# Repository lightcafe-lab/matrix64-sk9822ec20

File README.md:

# matrix64-sk9822ec20
 SK9822-EC20を使用した8×8のLEDマトリクスです<br><br>
LIGHTCAFE LAB LED-Cube ブログページ<br>
https://lab.lightcafe.co.jp/blog/ledcube-list<br><br>

<br>
## ライセンスについて
この 作品 は <a rel="license" href="https://creativecommons.org/licenses/by-sa/4.0/deed.ja">クリエイティブ・コモンズ 表示 - 継承 4.0 国際 ライセンス</a>の下に提供されています<br>
<br />

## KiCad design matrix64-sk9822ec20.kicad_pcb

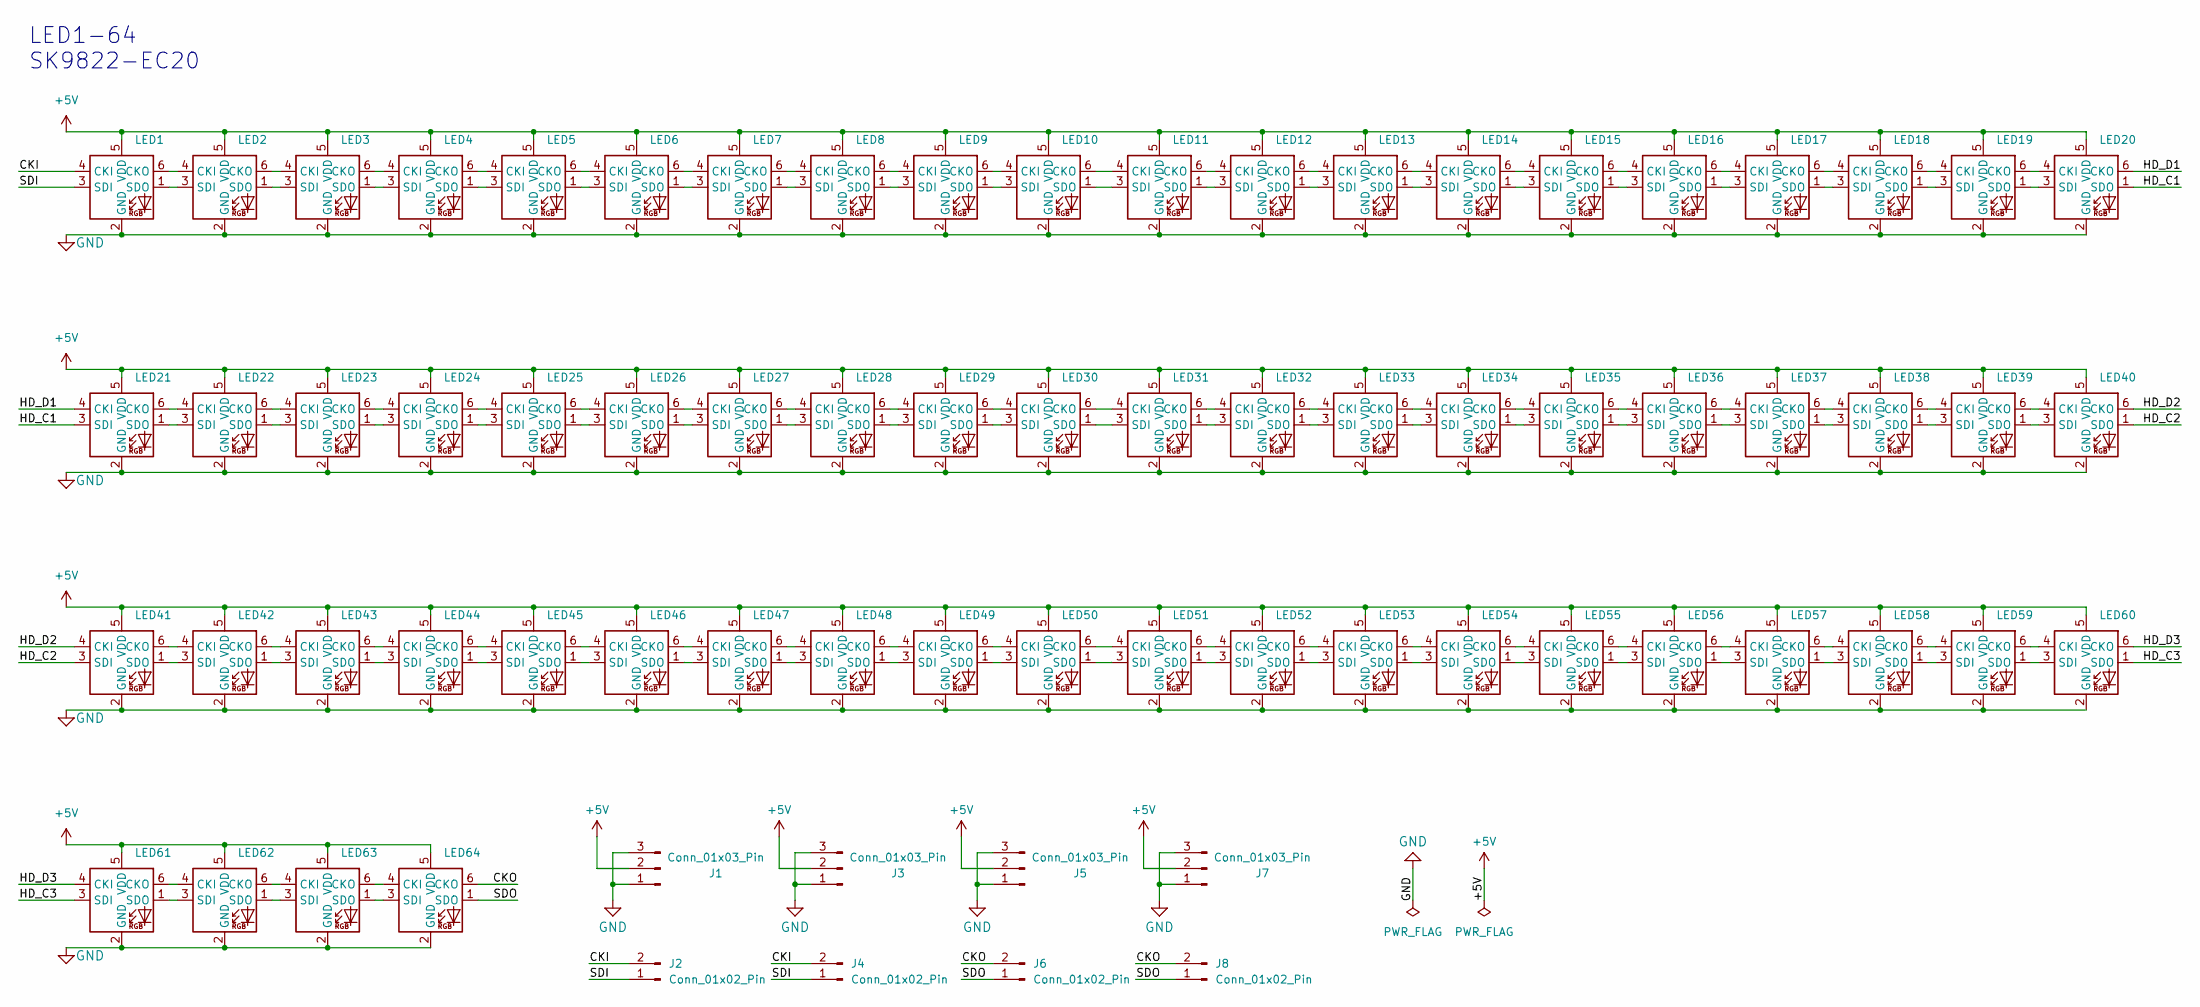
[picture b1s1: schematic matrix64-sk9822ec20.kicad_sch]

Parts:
J1, J3, J5, J7: Conn_01x03_Pin; 1×03_castell_power
J2, J4: Conn_01x02_Pin; 1x02_castell_signal_in
J6, J8: Conn_01x02_Pin; 1x02_castell_signal_out
LED1, LED2, LED3, LED4, LED5, LED6, LED7, LED8, LED9, LED10, LED11, LED12, LED13, LED14, LED15, LED16, LED17, LED18, LED19, LED20, LED21, LED22, LED23, LED24, LED25, LED26, LED27, LED28, LED29, LED30, LED31, LED32, LED33, LED34, LED35, LED36, LED37, LED38, LED39, LED40, LED41, LED42, LED43, LED44, LED45, LED46, LED47, LED48, LED49, LED50, LED51, LED52, LED53, LED54, LED55, LED56, LED57, LED58, LED59, LED60, LED61, LED62, LED63, LED64: SK9822-EC20

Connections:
+5V: J1.2, J3.2, J5.2, J7.2, LED1.5 (VDD), LED2.5 (VDD), LED3.5 (VDD), LED4.5 (VDD), LED5.5 (VDD), LED6.5 (VDD), LED7.5 (VDD), LED8.5 (VDD), LED9.5 (VDD), LED10.5 (VDD), LED11.5 (VDD), LED12.5 (VDD), LED13.5 (VDD), LED14.5 (VDD), LED15.5 (VDD), LED16.5 (VDD), LED17.5 (VDD), LED18.5 (VDD), LED19.5 (VDD), LED20.5 (VDD), LED21.5 (VDD), LED22.5 (VDD), LED23.5 (VDD), LED24.5 (VDD), LED25.5 (VDD), LED26.5 (VDD), LED27.5 (VDD), LED28.5 (VDD), LED29.5 (VDD), LED30.5 (VDD), LED31.5 (VDD), LED32.5 (VDD), LED33.5 (VDD), LED34.5 (VDD), LED35.5 (VDD), LED36.5 (VDD), LED37.5 (VDD), LED38.5 (VDD), LED39.5 (VDD), LED40.5 (VDD), LED41.5 (VDD), LED42.5 (VDD), LED43.5 (VDD), LED44.5 (VDD), LED45.5 (VDD), LED46.5 (VDD), LED47.5 (VDD), LED48.5 (VDD), LED49.5 (VDD), LED50.5 (VDD), LED51.5 (VDD), LED52.5 (VDD), LED53.5 (VDD), LED54.5 (VDD), LED55.5 (VDD), LED56.5 (VDD), LED57.5 (VDD), LED58.5 (VDD), LED59.5 (VDD), LED60.5 (VDD), LED61.5 (VDD), LED62.5 (VDD), LED63.5 (VDD), LED64.5 (VDD)
/CKI: J2.2, J4.2, LED1.4 (CKI)
/CKO: J6.2, J8.2, LED64.6 (CKO)
/HD_C1: LED20.1 (SDO), LED21.3 (SDI)
/HD_C2: LED40.1 (SDO), LED41.3 (SDI)
/HD_C3: LED60.1 (SDO), LED61.3 (SDI)
/HD_D1: LED20.6 (CKO), LED21.4 (CKI)
/HD_D2: LED40.6 (CKO), LED41.4 (CKI)
/HD_D3: LED60.6 (CKO), LED61.4 (CKI)
/SDI: J2.1, J4.1, LED1.3 (SDI)
/SDO: J6.1, J8.1, LED64.1 (SDO)
GND: J1.1, J1.3, J3.1, J3.3, J5.1, J5.3, J7.1, J7.3, LED1.2 (GND), LED2.2 (GND), LED3.2 (GND), LED4.2 (GND), LED5.2 (GND), LED6.2 (GND), LED7.2 (GND), LED8.2 (GND), LED9.2 (GND), LED10.2 (GND), LED11.2 (GND), LED12.2 (GND), LED13.2 (GND), LED14.2 (GND), LED15.2 (GND), LED16.2 (GND), LED17.2 (GND), LED18.2 (GND), LED19.2 (GND), LED20.2 (GND), LED21.2 (GND), LED22.2 (GND), LED23.2 (GND), LED24.2 (GND), LED25.2 (GND), LED26.2 (GND), LED27.2 (GND), LED28.2 (GND), LED29.2 (GND), LED30.2 (GND), LED31.2 (GND), LED32.2 (GND), LED33.2 (GND), LED34.2 (GND), LED35.2 (GND), LED36.2 (GND), LED37.2 (GND), LED38.2 (GND), LED39.2 (GND), LED40.2 (GND), LED41.2 (GND), LED42.2 (GND), LED43.2 (GND), LED44.2 (GND), LED45.2 (GND), LED46.2 (GND), LED47.2 (GND), LED48.2 (GND), LED49.2 (GND), LED50.2 (GND), LED51.2 (GND), LED52.2 (GND), LED53.2 (GND), LED54.2 (GND), LED55.2 (GND), LED56.2 (GND), LED57.2 (GND), LED58.2 (GND), LED59.2 (GND), LED60.2 (GND), LED61.2 (GND), LED62.2 (GND), LED63.2 (GND), LED64.2 (GND)
unnamed: LED1.6 (CKO), LED2.4 (CKI)
unnamed: LED1.1 (SDO), LED2.3 (SDI)
unnamed: LED2.6 (CKO), LED3.4 (CKI)
unnamed: LED2.1 (SDO), LED3.3 (SDI)
unnamed: LED3.6 (CKO), LED4.4 (CKI)
unnamed: LED3.1 (SDO), LED4.3 (SDI)
unnamed: LED4.6 (CKO), LED5.4 (CKI)
unnamed: LED4.1 (SDO), LED5.3 (SDI)
unnamed: LED5.6 (CKO), LED6.4 (CKI)
unnamed: LED5.1 (SDO), LED6.3 (SDI)
unnamed: LED6.6 (CKO), LED7.4 (CKI)
unnamed: LED6.1 (SDO), LED7.3 (SDI)
unnamed: LED7.6 (CKO), LED8.4 (CKI)
unnamed: LED7.1 (SDO), LED8.3 (SDI)
unnamed: LED8.6 (CKO), LED9.4 (CKI)
unnamed: LED8.1 (SDO), LED9.3 (SDI)
unnamed: LED9.6 (CKO), LED10.4 (CKI)
unnamed: LED10.6 (CKO), LED11.4 (CKI)
unnamed: LED9.1 (SDO), LED10.3 (SDI)
unnamed: LED10.1 (SDO), LED11.3 (SDI)
unnamed: LED11.6 (CKO), LED12.4 (CKI)
unnamed: LED11.1 (SDO), LED12.3 (SDI)
unnamed: LED12.6 (CKO), LED13.4 (CKI)
unnamed: LED12.1 (SDO), LED13.3 (SDI)
unnamed: LED13.6 (CKO), LED14.4 (CKI)
unnamed: LED13.1 (SDO), LED14.3 (SDI)
unnamed: LED14.6 (CKO), LED15.4 (CKI)
unnamed: LED14.1 (SDO), LED15.3 (SDI)
unnamed: LED15.6 (CKO), LED16.4 (CKI)
unnamed: LED15.1 (SDO), LED16.3 (SDI)
unnamed: LED16.6 (CKO), LED17.4 (CKI)
unnamed: LED16.1 (SDO), LED17.3 (SDI)
unnamed: LED17.6 (CKO), LED18.4 (CKI)
unnamed: LED17.1 (SDO), LED18.3 (SDI)
unnamed: LED18.6 (CKO), LED19.4 (CKI)
unnamed: LED18.1 (SDO), LED19.3 (SDI)
unnamed: LED19.6 (CKO), LED20.4 (CKI)
unnamed: LED19.1 (SDO), LED20.3 (SDI)
unnamed: LED21.6 (CKO), LED22.4 (CKI)
unnamed: LED21.1 (SDO), LED22.3 (SDI)
unnamed: LED22.6 (CKO), LED23.4 (CKI)
unnamed: LED22.1 (SDO), LED23.3 (SDI)
unnamed: LED23.6 (CKO), LED24.4 (CKI)
unnamed: LED23.1 (SDO), LED24.3 (SDI)
unnamed: LED24.6 (CKO), LED25.4 (CKI)
unnamed: LED24.1 (SDO), LED25.3 (SDI)
unnamed: LED25.6 (CKO), LED26.4 (CKI)
unnamed: LED25.1 (SDO), LED26.3 (SDI)
unnamed: LED26.6 (CKO), LED27.4 (CKI)
unnamed: LED26.1 (SDO), LED27.3 (SDI)
unnamed: LED27.6 (CKO), LED28.4 (CKI)
unnamed: LED27.1 (SDO), LED28.3 (SDI)
unnamed: LED28.6 (CKO), LED29.4 (CKI)
unnamed: LED28.1 (SDO), LED29.3 (SDI)
unnamed: LED29.6 (CKO), LED30.4 (CKI)
unnamed: LED29.1 (SDO), LED30.3 (SDI)
unnamed: LED30.6 (CKO), LED31.4 (CKI)
unnamed: LED30.1 (SDO), LED31.3 (SDI)
unnamed: LED31.6 (CKO), LED32.4 (CKI)
unnamed: LED31.1 (SDO), LED32.3 (SDI)
unnamed: LED32.6 (CKO), LED33.4 (CKI)
unnamed: LED32.1 (SDO), LED33.3 (SDI)
unnamed: LED33.6 (CKO), LED34.4 (CKI)
unnamed: LED33.1 (SDO), LED34.3 (SDI)
unnamed: LED34.6 (CKO), LED35.4 (CKI)
unnamed: LED34.1 (SDO), LED35.3 (SDI)
unnamed: LED35.6 (CKO), LED36.4 (CKI)
unnamed: LED35.1 (SDO), LED36.3 (SDI)
unnamed: LED36.6 (CKO), LED37.4 (CKI)
unnamed: LED36.1 (SDO), LED37.3 (SDI)
unnamed: LED37.6 (CKO), LED38.4 (CKI)
unnamed: LED37.1 (SDO), LED38.3 (SDI)
unnamed: LED38.6 (CKO), LED39.4 (CKI)
unnamed: LED38.1 (SDO), LED39.3 (SDI)
unnamed: LED39.6 (CKO), LED40.4 (CKI)
unnamed: LED39.1 (SDO), LED40.3 (SDI)
unnamed: LED41.6 (CKO), LED42.4 (CKI)
unnamed: LED41.1 (SDO), LED42.3 (SDI)
unnamed: LED42.6 (CKO), LED43.4 (CKI)
unnamed: LED42.1 (SDO), LED43.3 (SDI)
unnamed: LED43.6 (CKO), LED44.4 (CKI)
unnamed: LED43.1 (SDO), LED44.3 (SDI)
unnamed: LED44.6 (CKO), LED45.4 (CKI)
unnamed: LED44.1 (SDO), LED45.3 (SDI)
unnamed: LED45.6 (CKO), LED46.4 (CKI)
unnamed: LED45.1 (SDO), LED46.3 (SDI)
unnamed: LED46.6 (CKO), LED47.4 (CKI)
unnamed: LED46.1 (SDO), LED47.3 (SDI)
unnamed: LED47.6 (CKO), LED48.4 (CKI)
unnamed: LED47.1 (SDO), LED48.3 (SDI)
unnamed: LED48.6 (CKO), LED49.4 (CKI)
unnamed: LED48.1 (SDO), LED49.3 (SDI)
unnamed: LED49.6 (CKO), LED50.4 (CKI)
unnamed: LED49.1 (SDO), LED50.3 (SDI)
unnamed: LED50.6 (CKO), LED51.4 (CKI)
unnamed: LED50.1 (SDO), LED51.3 (SDI)
unnamed: LED51.6 (CKO), LED52.4 (CKI)
unnamed: LED51.1 (SDO), LED52.3 (SDI)
unnamed: LED52.6 (CKO), LED53.4 (CKI)
unnamed: LED52.1 (SDO), LED53.3 (SDI)
unnamed: LED53.6 (CKO), LED54.4 (CKI)
unnamed: LED53.1 (SDO), LED54.3 (SDI)
unnamed: LED54.6 (CKO), LED55.4 (CKI)
unnamed: LED54.1 (SDO), LED55.3 (SDI)
unnamed: LED55.6 (CKO), LED56.4 (CKI)
unnamed: LED55.1 (SDO), LED56.3 (SDI)
unnamed: LED56.6 (CKO), LED57.4 (CKI)
unnamed: LED56.1 (SDO), LED57.3 (SDI)
unnamed: LED57.6 (CKO), LED58.4 (CKI)
unnamed: LED57.1 (SDO), LED58.3 (SDI)
unnamed: LED58.6 (CKO), LED59.4 (CKI)
unnamed: LED58.1 (SDO), LED59.3 (SDI)
unnamed: LED59.6 (CKO), LED60.4 (CKI)
unnamed: LED59.1 (SDO), LED60.3 (SDI)
unnamed: LED61.6 (CKO), LED62.4 (CKI)
unnamed: LED61.1 (SDO), LED62.3 (SDI)
unnamed: LED62.6 (CKO), LED63.4 (CKI)
unnamed: LED62.1 (SDO), LED63.3 (SDI)
unnamed: LED63.6 (CKO), LED64.4 (CKI)
unnamed: LED63.1 (SDO), LED64.3 (SDI)

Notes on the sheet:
LED1-64 SK9822-EC20

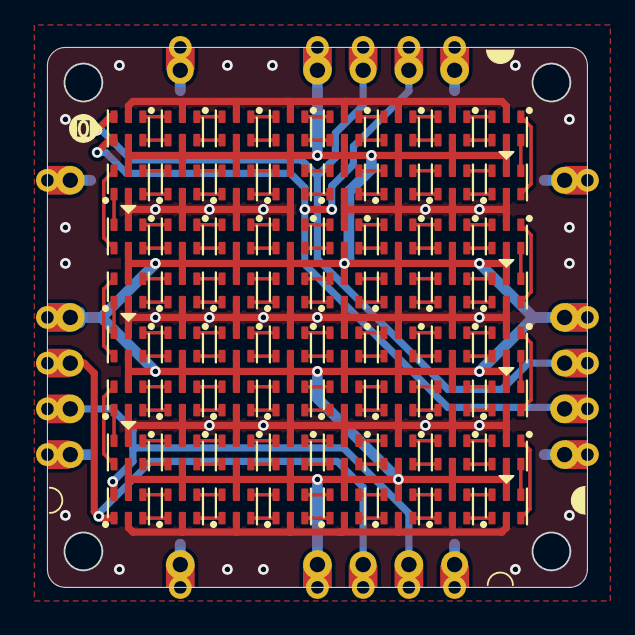
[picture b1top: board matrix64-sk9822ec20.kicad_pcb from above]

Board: 2 copper layers, 30.0 x 30.0 mm, 72 parts (0 on the bottom side), 132 nets.

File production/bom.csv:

Designator,Footprint,Quantity,Value,LCSC Part #
"J1, J3, J5, J7",1×03_castell_power,4,Conn_01x03_Pin,
"J2, J4",1x02_castell_signal_in,2,Conn_01x02_Pin,
"J6, J8",1x02_castell_signal_out,2,Conn_01x02_Pin,
"LED1, LED10, LED11, LED12, LED13, LED14, LED15, LED16, LED17, LED18, LED19, LED2, LED20, LED21, LED22, LED23, LED24, LED25, LED26, LED27, LED28, LED29, LED3, LED30, LED31, LED32, LED33, LED34, LED35, LED36, LED37, LED38, LED39, LED4, LED40, LED41, LED42, LED43, LED44, LED45, LED46, LED47, LED48, LED49, LED5, LED50, LED51, LED52, LED53, LED54, LED55, LED56, LED57, LED58, LED59, LED6, LED60, LED61, LED62, LED63, LED64, LED7, LED8, LED9",SK9822-EC20,64,SK9822-EC20,

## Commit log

2025-03-18 add LICENSE
2025-03-18 add readme
2025-03-18 rename pdf
2025-03-18 update kicad-files
2025-03-21 add arduino sketch
2025-03-27 add 3dprint

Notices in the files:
README.md:
CC BY-SA 4.0
